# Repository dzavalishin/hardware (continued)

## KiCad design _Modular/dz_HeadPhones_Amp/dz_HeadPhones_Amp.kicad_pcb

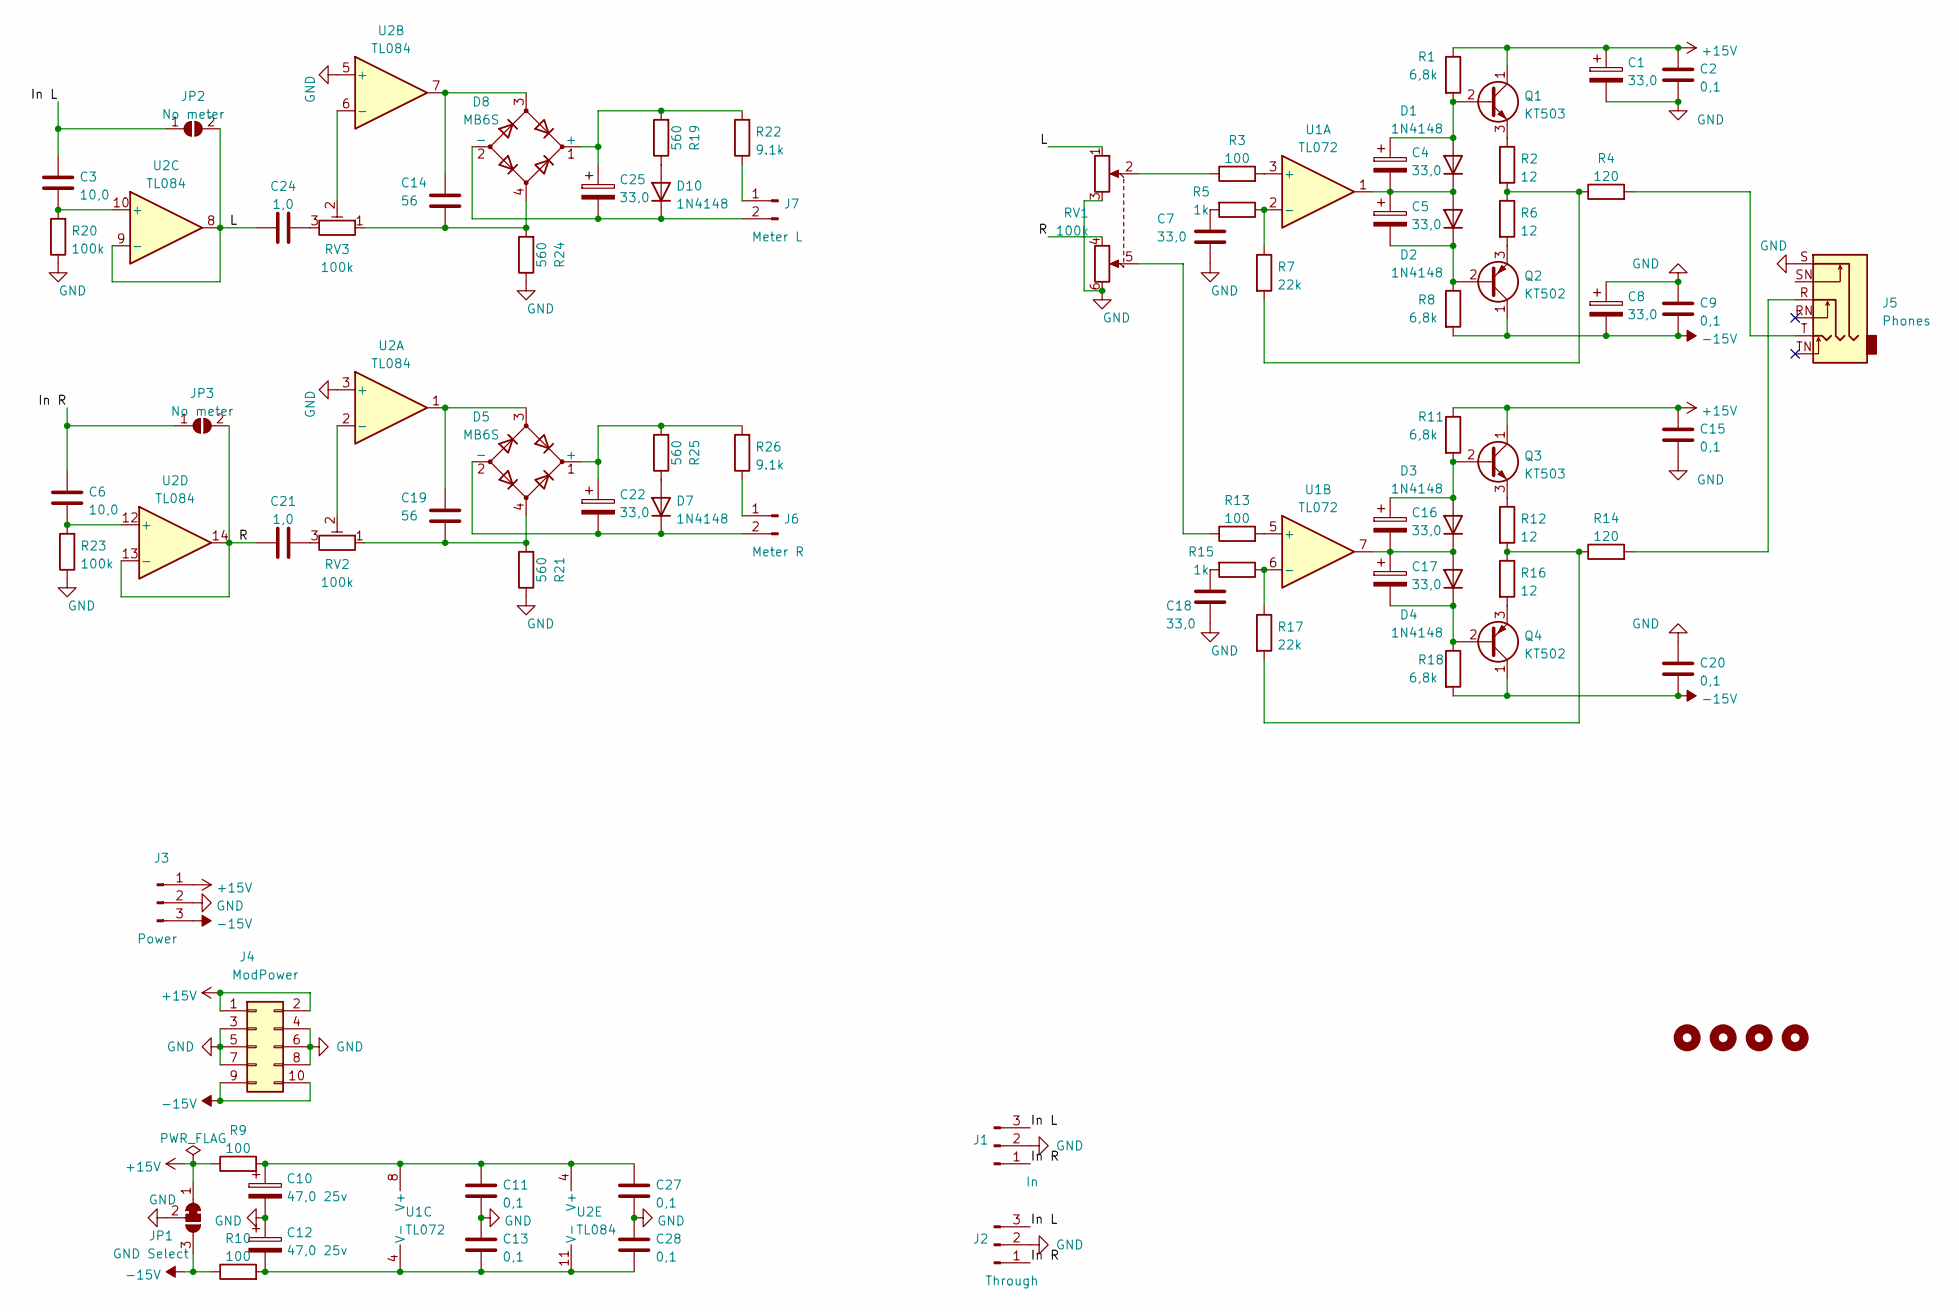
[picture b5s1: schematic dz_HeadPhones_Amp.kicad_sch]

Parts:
C1, C4, C5, C7, C8, C16, C17, C18, C22, C25: 33,0; CP_Radial_D5.0mm_P2.50mm
C2, C9, C11, C13, C15, C20, C27, C28: 0,1; C_1206_3216Metric_Pad1.33x1.80mm_HandSolder
C3, C6: 10,0; C_0805_2012Metric_Pad1.18x1.45mm_HandSolder
C10, C12: 47,0 25v; CP_Radial_D5.0mm_P2.50mm
C14, C19: 56; C_Disc_D5.0mm_W2.5mm_P2.50mm
C21, C24: 1,0; C_0805_2012Metric_Pad1.18x1.45mm_HandSolder
D1, D2, D3, D4, D7, D10: 1N4148; D_DO-35_SOD27_P2.54mm_Vertical_KathodeUp
D5, D8: MB6S; TO-269AA
H1, H2, H3, H4: MountingHole; MountingHole_3.2mm_M3
J1: In; PinHeader_1x03_P2.54mm_Vertical
J2: Through; PinHeader_1x03_P2.54mm_Vertical
J3: Power; PinHeader_1x03_P2.54mm_Vertical
J4: ModPower; PinHeader_2x05_P2.54mm_Vertical
J5: Phones; Jack_6.35mm_Neutrik_NMJ6HCD2_Horizontal
J6: Meter R; PinHeader_1x02_P2.54mm_Vertical
J7: Meter L; PinHeader_1x02_P2.54mm_Vertical
JP1: GND Select; PinHeader_1x03_P2.54mm_Vertical
JP2, JP3: No meter; PinHeader_1x02_P2.54mm_Vertical
Q1, Q3: КТ503; TO-92_Inline
Q2, Q4: КТ502; TO-92_Inline
R1, R8, R11, R18: 6,8k; R_Axial_DIN0207_L6.3mm_D2.5mm_P2.54mm_Vertical
R2, R6, R12, R16: 12; R_Axial_DIN0207_L6.3mm_D2.5mm_P2.54mm_Vertical
R3, R9, R10, R13: 100; R_Axial_DIN0207_L6.3mm_D2.5mm_P2.54mm_Vertical
R4, R14: 120; R_Axial_DIN0207_L6.3mm_D2.5mm_P2.54mm_Vertical
R5, R15: 1k; R_Axial_DIN0207_L6.3mm_D2.5mm_P2.54mm_Vertical
R7, R17: 22k; R_Axial_DIN0207_L6.3mm_D2.5mm_P2.54mm_Vertical
R19, R21, R24, R25: 560; R_Axial_DIN0207_L6.3mm_D2.5mm_P2.54mm_Vertical
R20, R23: 100k; R_Axial_DIN0207_L6.3mm_D2.5mm_P2.54mm_Vertical
R22, R26: 9.1k; R_Axial_DIN0207_L6.3mm_D2.5mm_P2.54mm_Vertical
RV1: 100k; Potentiometer_Alps_RK097_Dual_Horizontal
RV2, RV3: 100k; Potentiometer_Runtron_RM-065_Vertical
U1: TL072; DIP-8_W7.62mm_Socket_LongPads
U2: TL084; DIP-14_W7.62mm_Socket_LongPads

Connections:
+15V: C1.1, C2.1, C15.1, J3.1, J4.1, J4.2, JP1.1 (A), Q1.1 (C), Q3.1 (C), R1.1, R9.1, R11.1
-15V: C8.2, C9.2, C20.2, J3.3, J4.9, J4.10, JP1.3 (B), Q2.1 (C), Q4.1 (C), R8.2, R10.1, R18.2
/In L: C3.1, J1.3, J2.3, JP2.1 (A)
/In R: C6.1, J1.1, J2.1, JP3.1 (A)
/L: C24.1, JP2.2 (B), RV1.1, U2.8, U2.9 (-)
/R: C21.1, JP3.2 (B), RV1.4, U2.13 (-), U2.14
GND: C1.2, C2.2, C7.2, C8.1, C9.1, C10.2, C11.2, C12.1, C13.1, C15.2, C18.2, C20.1, C27.2, C28.1, J1.2, J2.2, J3.2, J4.3, J4.4, J4.5, J4.6, J4.7, J4.8, J5.S, JP1.2 (C), R20.1, R21.1, R23.1, R24.1, RV1.3, RV1.6, U2.3 (+), U2.5 (+)
unnamed: C3.2, R20.2, U2.10 (+)
unnamed: C4.1, D1.2 (A), Q1.2 (B), R1.2
unnamed: C4.2, C5.1, D1.1 (K), D2.2 (A), U1.1
unnamed: C5.2, D2.1 (K), Q2.2 (B), R8.1
unnamed: C6.2, R23.2, U2.12 (+)
unnamed: C7.1, R5.2
unnamed: C10.1, C11.1, C27.1, R9.2, U1.8 (V+), U2.4 (V+)
unnamed: C12.2, C13.2, C28.2, R10.2, U1.4 (V-), U2.11 (V-)
unnamed: C16.1, D3.2 (A), Q3.2 (B), R11.2
unnamed: C16.2, C17.1, D3.1 (K), D4.2 (A), U1.7
unnamed: C17.2, D4.1 (K), Q4.2 (B), R18.1
unnamed: C18.1, R15.2
unnamed: C21.2, RV2.3
unnamed: C22.1, D5.1 (+), R25.2, R26.2
unnamed: C22.2, D5.2 (-), D7.1 (K), J6.2
unnamed: C25.1, D8.1 (+), R19.2, R22.2
unnamed: C25.2, D8.2 (-), D10.1 (K), J7.2
unnamed: C19.1, D5.3, U2.1
unnamed: D7.2 (A), R25.1
unnamed: C14.1, D8.3, U2.7
unnamed: C14.2, D8.4, R24.2, RV3.1
unnamed: D10.2 (A), R19.1
unnamed: J5.R, R14.2
unnamed: J5.T, R4.2
unnamed: J6.1, R26.1
unnamed: J7.1, R22.1
unnamed: Q1.3 (E), R2.1
unnamed: Q2.3 (E), R6.2
unnamed: Q3.3 (E), R12.1
unnamed: Q4.3 (E), R16.2
unnamed: R2.2, R4.1, R6.1, R7.2
unnamed: R3.1, RV1.2
unnamed: R3.2, U1.3 (+)
unnamed: R5.1, R7.1, U1.2 (-)
unnamed: R12.2, R14.1, R16.1, R17.2
unnamed: R13.1, RV1.5
unnamed: R13.2, U1.5 (+)
unnamed: R15.1, R17.1, U1.6 (-)
unnamed: C19.2, D5.4, R21.2, RV2.1
unnamed: RV3.2, U2.6 (-)
unnamed: C24.2, RV3.3
unnamed: RV2.2, U2.2 (-)

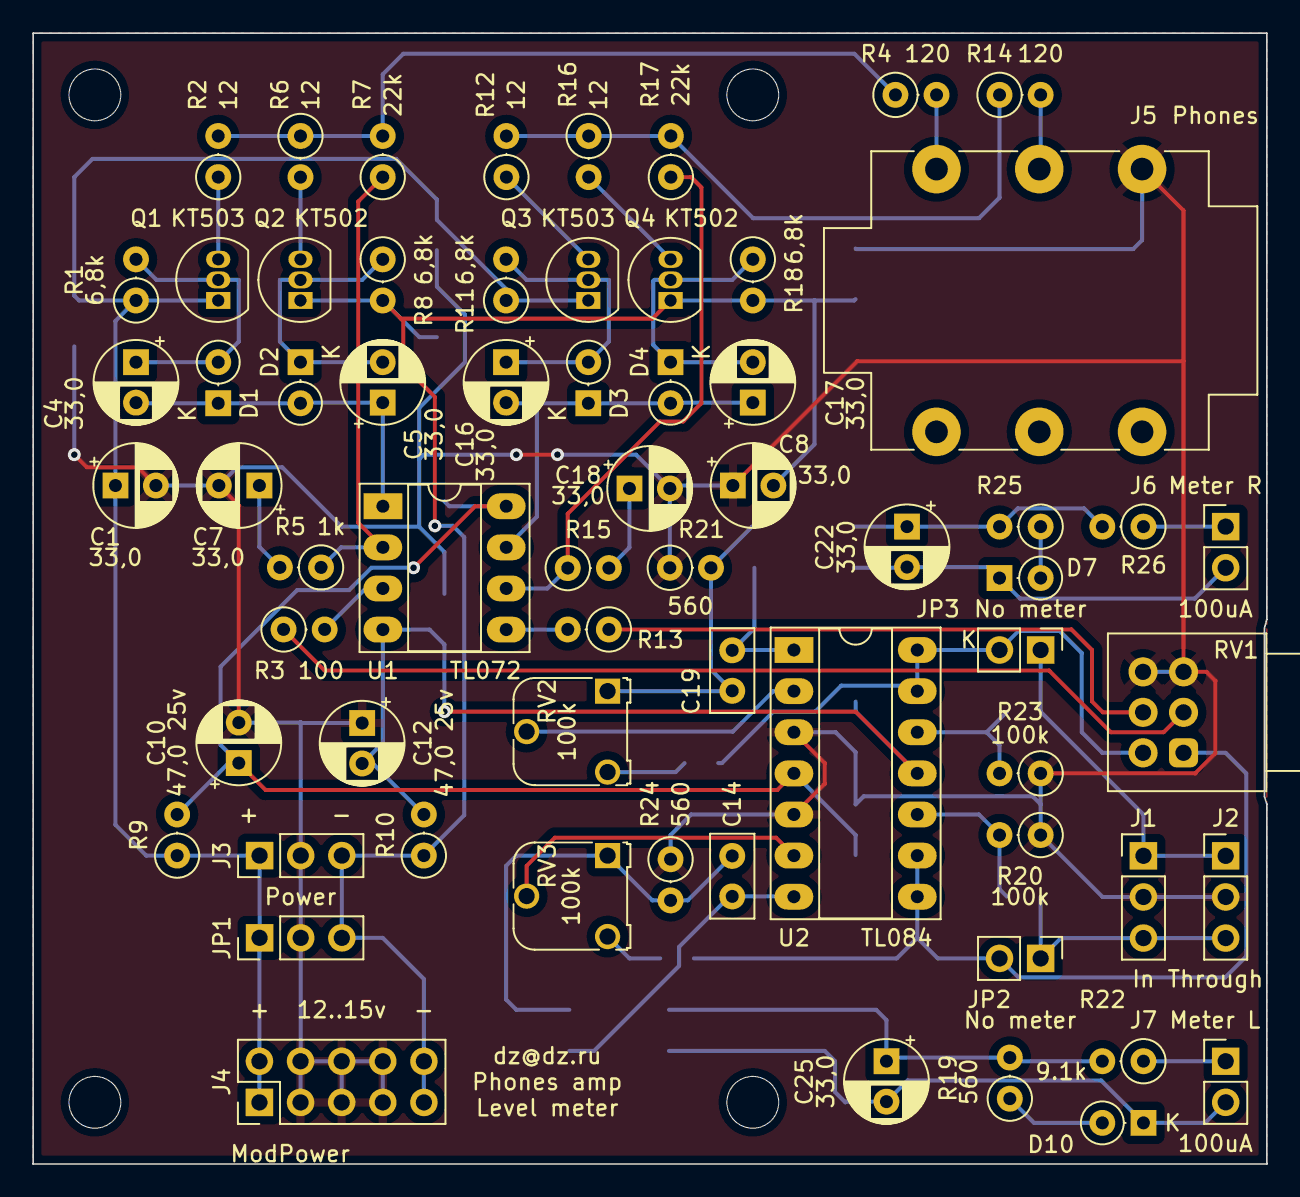
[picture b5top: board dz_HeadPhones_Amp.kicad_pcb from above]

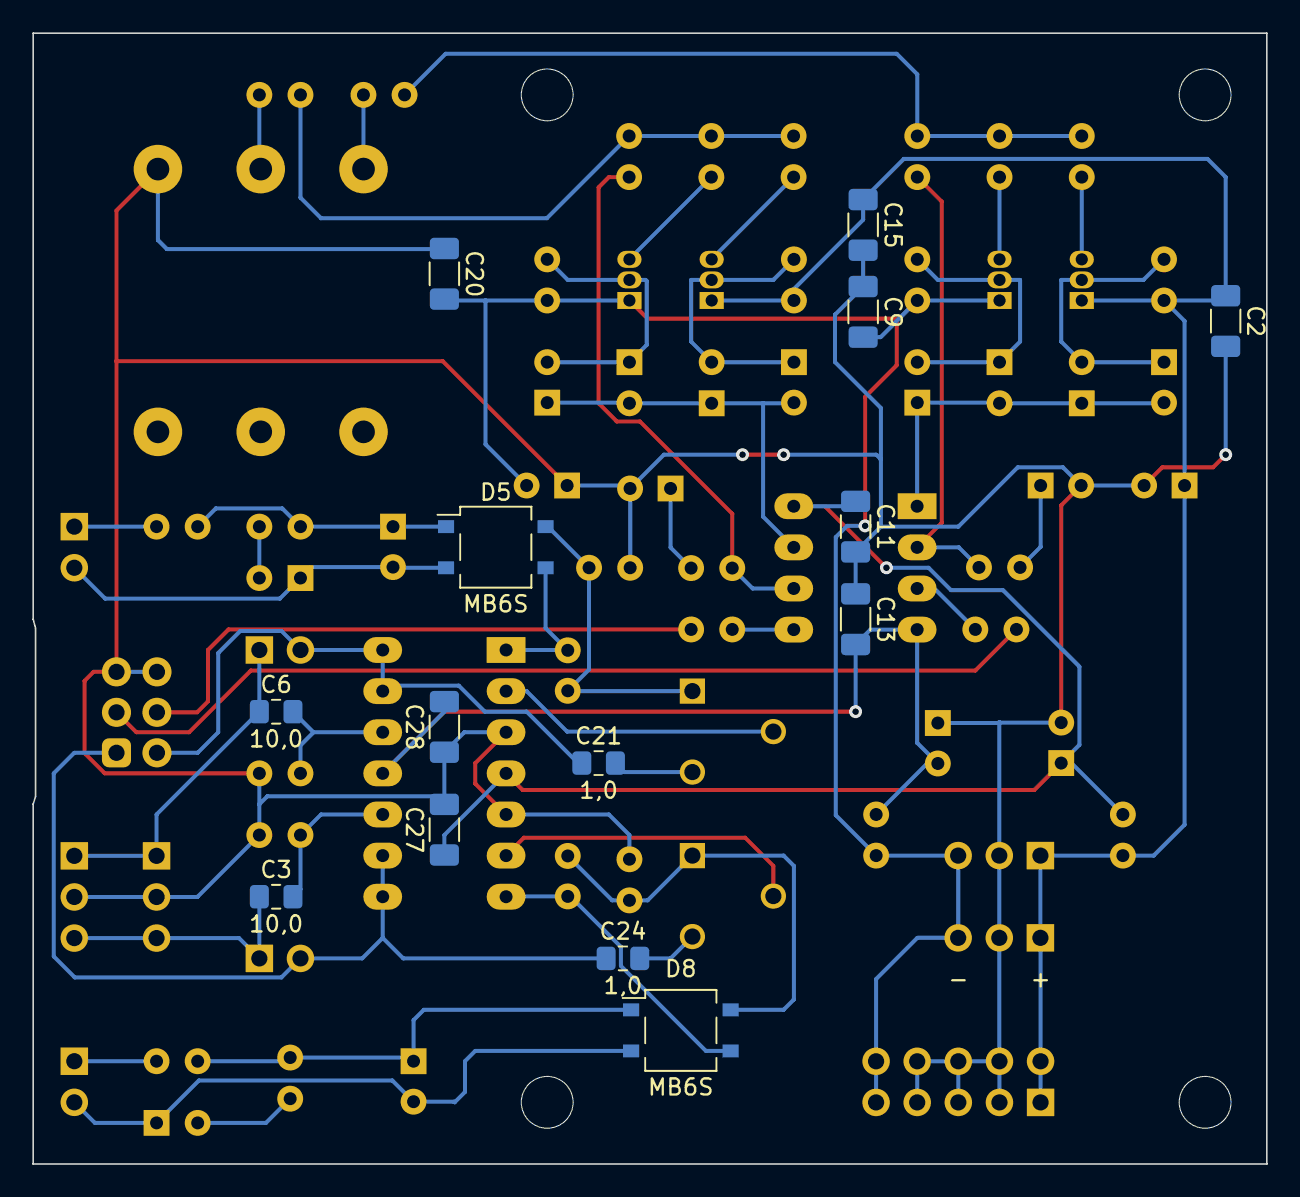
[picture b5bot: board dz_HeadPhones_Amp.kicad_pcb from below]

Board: 2 copper layers, 76.2 x 69.8 mm, 83 parts (14 on the bottom side), 49 nets.

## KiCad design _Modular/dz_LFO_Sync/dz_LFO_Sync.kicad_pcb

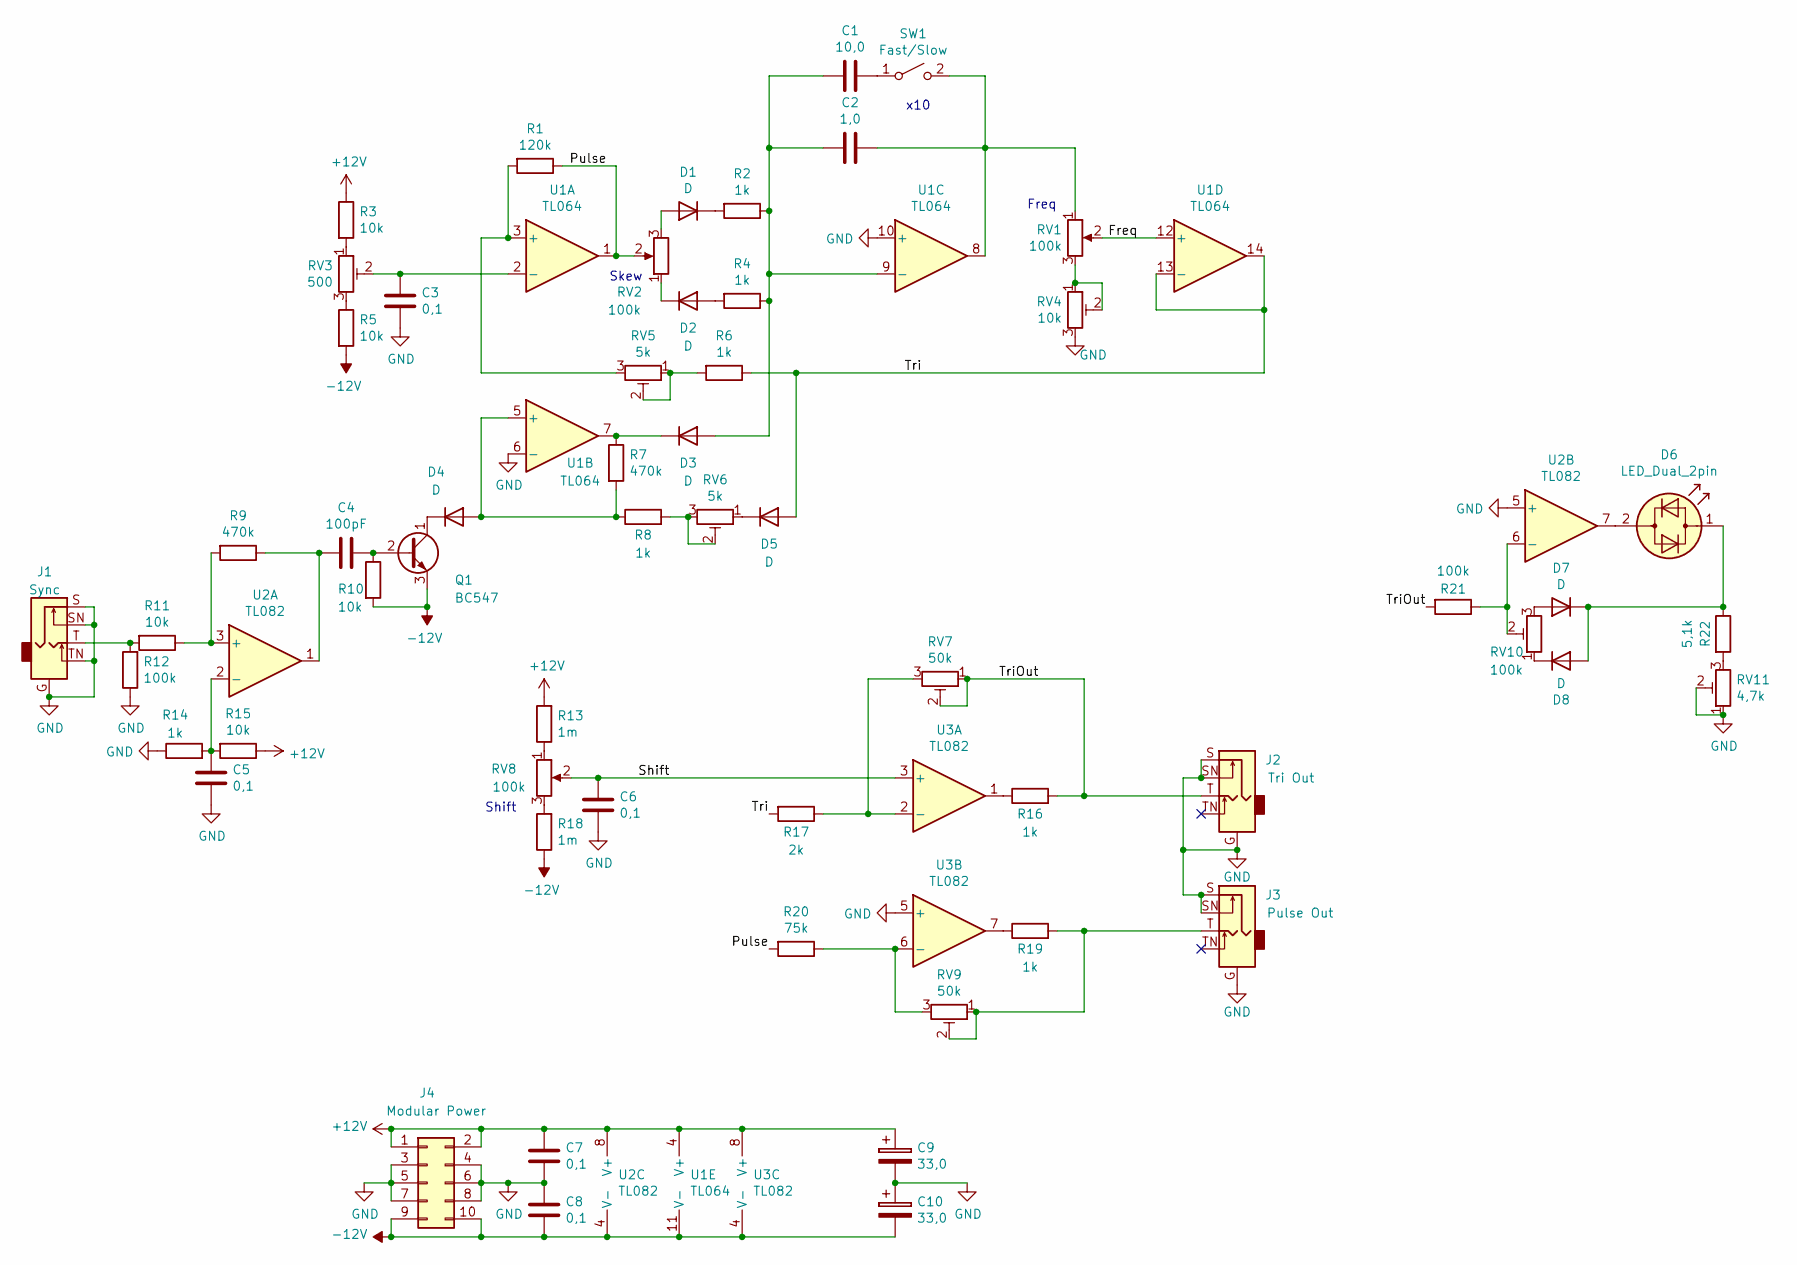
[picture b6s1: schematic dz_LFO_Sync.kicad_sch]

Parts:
C1: 10,0; C_0805_2012Metric_Pad1.18x1.45mm_HandSolder
C2: 1,0; C_0805_2012Metric_Pad1.18x1.45mm_HandSolder
C3, C5, C6, C7, C8: 0,1; C_0805_2012Metric_Pad1.18x1.45mm_HandSolder
C4: 100pF; C_0805_2012Metric_Pad1.18x1.45mm_HandSolder
C9, C10: 33,0; CP_Radial_D7.5mm_P2.50mm
D1, D2, D3, D4, D5, D7, D8: D; D_MicroMELF_Handsoldering
D6: LED_Dual_2pin; LED_D3.0mm_Horizontal_O1.27mm_Z6.0mm
J1: Sync; Jack_3.5mm_CUI_SJ1-3525N_Horizontal
J2: Tri Out; Jack_3.5mm_CUI_SJ1-3525N_Horizontal
J3: Pulse Out; Jack_3.5mm_CUI_SJ1-3525N_Horizontal
J4: Modular Power; PinHeader_2x05_P2.54mm_Vertical
Q1: BC547; TO-92_Inline
R1: 120k; R_0805_2012Metric_Pad1.20x1.40mm_HandSolder
R2, R4, R6, R8, R14, R16, R19: 1k; R_0805_2012Metric_Pad1.20x1.40mm_HandSolder
R3, R5, R10, R11, R15: 10k; R_0805_2012Metric_Pad1.20x1.40mm_HandSolder
R7, R9: 470k; R_0805_2012Metric_Pad1.20x1.40mm_HandSolder
R12, R21: 100k; R_0805_2012Metric_Pad1.20x1.40mm_HandSolder
R13, R18: 1m; R_0805_2012Metric_Pad1.20x1.40mm_HandSolder
R17: 2k; R_0805_2012Metric_Pad1.20x1.40mm_HandSolder
R20: 75k; R_0805_2012Metric_Pad1.20x1.40mm_HandSolder
R22: 5,1k; R_0805_2012Metric_Pad1.20x1.40mm_HandSolder
RV1, RV2, RV8: 100k; Potentiometer_Alps_RK097_Single_Horizontal
RV3: 500; Potentiometer_Runtron_RM-065_Vertical
RV4: 10k; Potentiometer_Runtron_RM-065_Vertical
RV5, RV6: 5k; Potentiometer_Runtron_RM-065_Vertical
RV7, RV9: 50k; Potentiometer_Runtron_RM-065_Vertical
RV10: 100k; Potentiometer_Runtron_RM-065_Vertical
RV11: 4,7k; Potentiometer_Runtron_RM-065_Vertical
SW1: Fast/Slow; PinHeader_1x02_P2.54mm_Vertical
U1: TL064; DIP-14_W7.62mm_Socket_LongPads
U2, U3: TL082; DIP-8_W7.62mm_Socket_LongPads

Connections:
+12V: C7.1, C9.1, J4.1, J4.2, R3.1, R13.2, R15.1, U1.4 (V+), U2.8 (V+), U3.8 (V+)
-12V: C8.2, C10.2, J4.9, J4.10, Q1.3 (E), R5.2, R10.2, R18.1, U1.11 (V-), U2.4 (V-), U3.4 (V-)
/Freq: RV1.2, U1.12 (+)
/Pulse: R1.1, R20.2, RV2.2, U1.1
/Shift: C6.1, RV8.2, U3.3 (+)
/Tri: D5.2 (A), R6.1, R17.2, U1.13 (-), U1.14
/TriOut: J2.T, R16.2, R21.2, RV7.1, RV7.2
GND: C3.2, C5.2, C6.2, C7.2, C8.1, C9.2, C10.1, J1.G, J1.S, J1.SN, J1.TN, J2.G, J2.S, J2.SN, J3.G, J3.S, J3.SN, J4.3, J4.4, J4.5, J4.6, J4.7, J4.8, R12.1, R14.1, RV4.3, RV11.1, RV11.2, U1.6 (-), U1.10 (+), U2.5 (+), U3.5 (+)
unnamed: C1.1, SW1.1 (A)
unnamed: C1.2, C2.2, D3.2 (A), R2.1, R4.1, U1.9 (-)
unnamed: C2.1, RV1.1, SW1.2 (B), U1.8
unnamed: C3.1, RV3.2, U1.2 (-)
unnamed: C4.1, Q1.2 (B), R10.1
unnamed: C4.2, R9.1, U2.1
unnamed: C5.1, R14.2, R15.2, U2.2 (-)
unnamed: D1.1 (K), R2.2
unnamed: D1.2 (A), RV2.3
unnamed: D2.1 (K), RV2.1
unnamed: D2.2 (A), R4.2
unnamed: D3.1 (K), R7.1, U1.7
unnamed: D4.1 (K), Q1.1 (C)
unnamed: D4.2 (A), R7.2, R8.1, U1.5 (+)
unnamed: D5.1 (K), RV6.1
unnamed: D6.1 (KA), D7.1 (K), D8.2 (A), R22.1
unnamed: D6.2 (AK), U2.7
unnamed: D7.2 (A), RV10.3
unnamed: D8.1 (K), RV10.1
unnamed: R1.2, RV5.3, U1.3 (+)
unnamed: R3.2, RV3.1
unnamed: R5.1, RV3.3
unnamed: R6.2, RV5.1, RV5.2
unnamed: R8.2, RV6.2, RV6.3
unnamed: R9.2, R11.1, U2.3 (+)
unnamed: J1.T, R11.2, R12.2
unnamed: R13.1, RV8.1
unnamed: R16.1, U3.1
unnamed: R17.1, RV7.3, U3.2 (-)
unnamed: R18.2, RV8.3
unnamed: R19.1, U3.7
unnamed: J3.T, R19.2, RV9.1, RV9.2
unnamed: R20.1, RV9.3, U3.6 (-)
unnamed: R21.1, RV10.2, U2.6 (-)
unnamed: R22.2, RV11.3
unnamed: RV1.3, RV4.1, RV4.2

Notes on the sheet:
Shift
Freq
Skew
x10

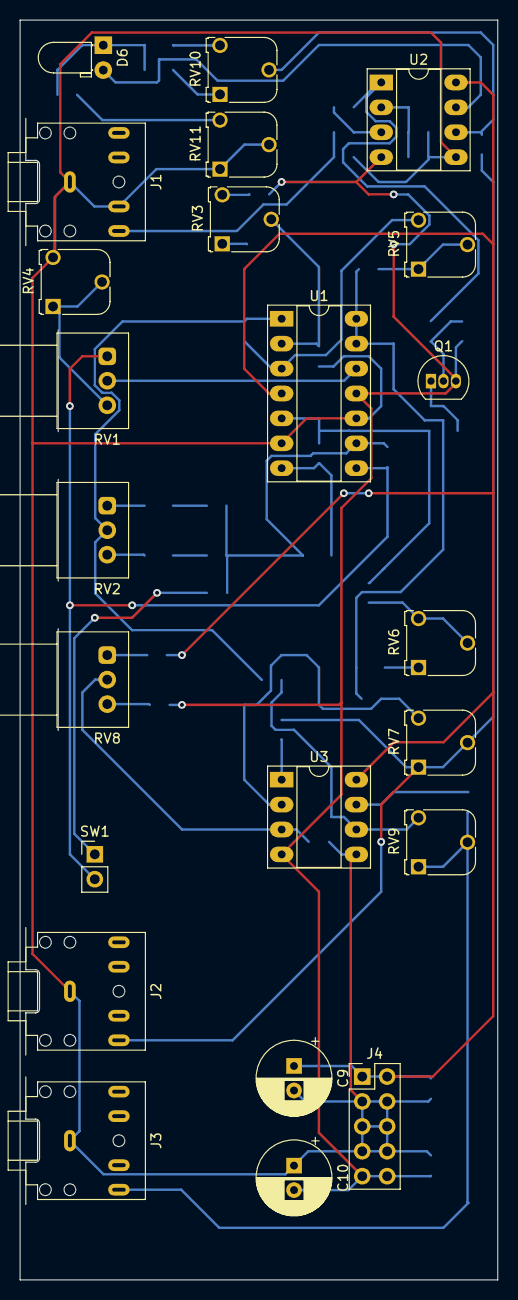
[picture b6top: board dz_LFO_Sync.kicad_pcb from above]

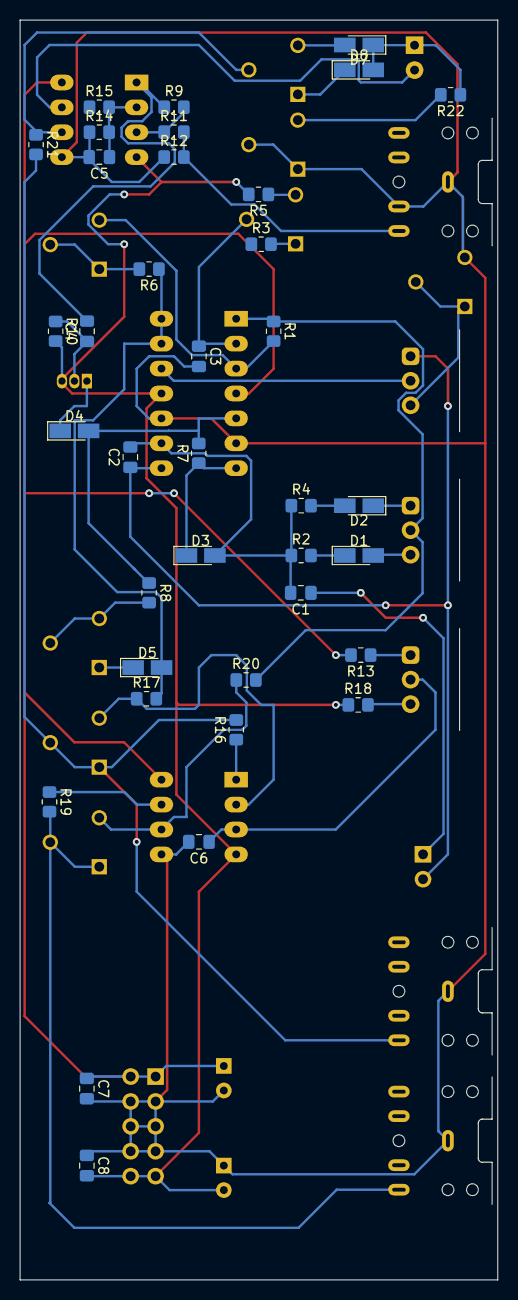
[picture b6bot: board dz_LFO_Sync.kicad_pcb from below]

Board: 2 copper layers, 48.7 x 128.5 mm, 60 parts (37 on the bottom side), 44 nets.

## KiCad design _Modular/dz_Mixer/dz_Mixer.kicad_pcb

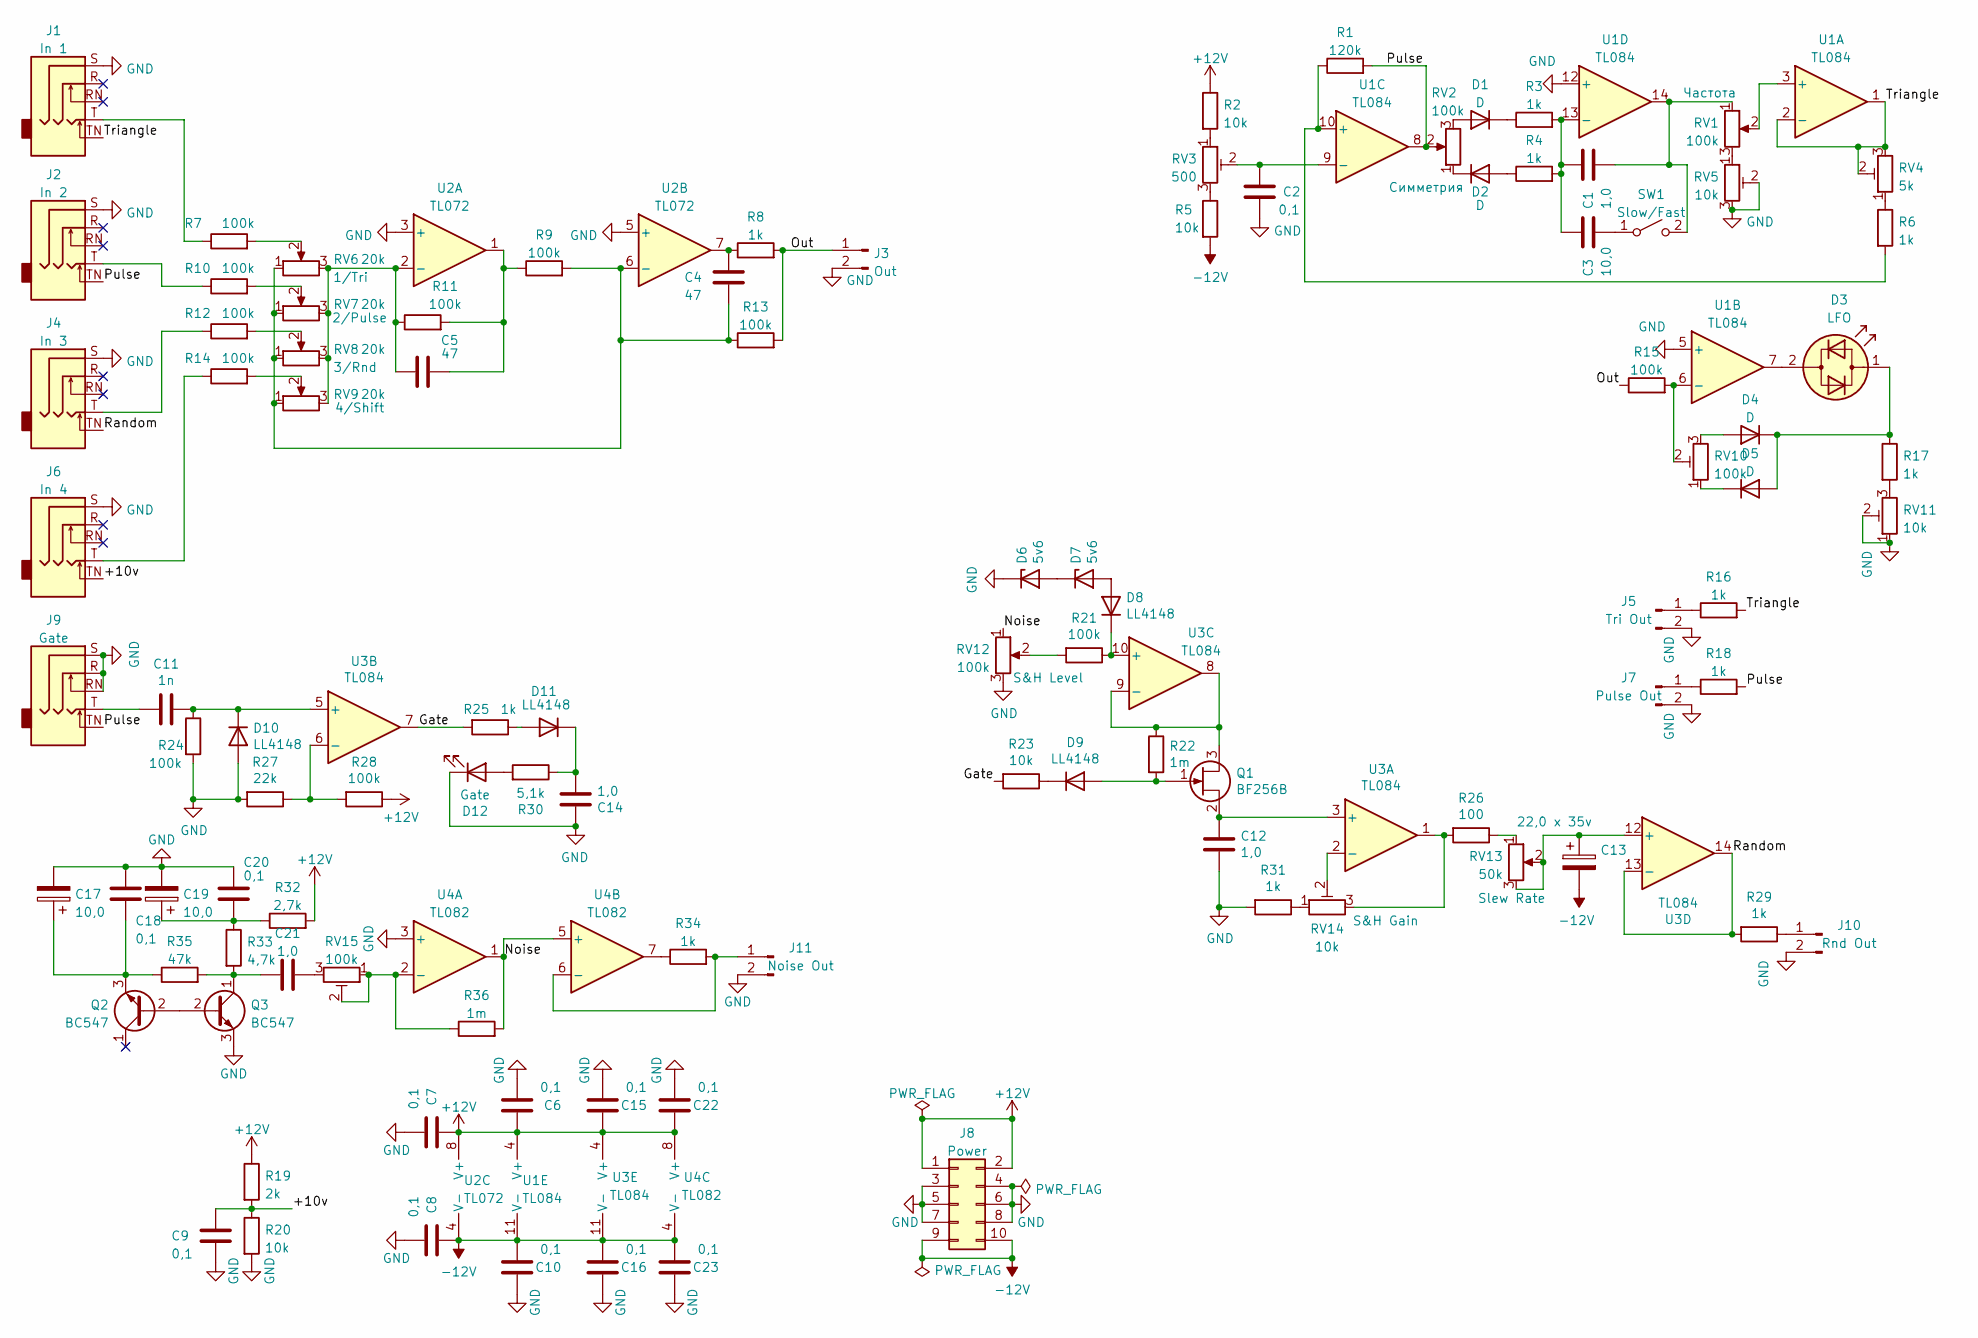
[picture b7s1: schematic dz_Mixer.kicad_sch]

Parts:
C1, C12, C14, C21: 1,0; C_1206_3216Metric_Pad1.33x1.80mm_HandSolder
C2, C6, C7, C8, C9, C10, C15, C16, C18, C20, C22, C23: 0,1; C_1206_3216Metric_Pad1.33x1.80mm_HandSolder
C3: 10,0; C_0805_2012Metric_Pad1.18x1.45mm_HandSolder
C4, C5: 47; C_1206_3216Metric_Pad1.33x1.80mm_HandSolder
C11: 1n; C_1206_3216Metric_Pad1.33x1.80mm_HandSolder
C13: 22,0 x 35v; CP_Radial_D8.0mm_P2.50mm
C17, C19: 10,0; CP_Elec_4x5.4
D1, D2, D4, D5: D; D_MiniMELF_Handsoldering
D3: LFO; LED_D3.0mm
D6, D7: 5v6; D_MiniMELF_Handsoldering
D8, D9, D10, D11: LL4148; D_MiniMELF_Handsoldering
D12: Gate; LED_D3.0mm_Horizontal_O1.27mm_Z2.0mm
J1: In 1; Jack_3.5mm_CUI_SJ1-3525N_Horizontal
J2: In 2; Jack_3.5mm_CUI_SJ1-3525N_Horizontal
J3: Out; PinHeader_1x02_P2.54mm_Vertical
J4: In 3; Jack_3.5mm_CUI_SJ1-3525N_Horizontal
J5: Tri Out; PinHeader_1x02_P2.54mm_Vertical
J6: In 4; Jack_3.5mm_CUI_SJ1-3525N_Horizontal
J7: Pulse Out; PinHeader_1x02_P2.54mm_Vertical
J8: Power; PinHeader_2x05_P2.54mm_Vertical
J9: Gate; Jack_3.5mm_CUI_SJ1-3525N_Horizontal
J10: Rnd Out; PinHeader_1x02_P2.54mm_Vertical
J11: Noise Out; PinHeader_1x02_P2.54mm_Vertical
Q1: BF256B; TO-92
Q2, Q3: BC547; TO-92
R1: 120k; R_1206_3216Metric_Pad1.30x1.75mm_HandSolder
R2, R5, R20, R23: 10k; R_1206_3216Metric_Pad1.30x1.75mm_HandSolder
R3, R4, R6, R8, R16, R17, R18, R25, R29, R31, R34: 1k; R_1206_3216Metric_Pad1.30x1.75mm_HandSolder
R7, R9, R10, R11, R12, R13, R14, R15, R21, R24, R28: 100k; R_1206_3216Metric_Pad1.30x1.75mm_HandSolder
R19: 2k; R_1206_3216Metric_Pad1.30x1.75mm_HandSolder
R22, R36: 1m; R_1206_3216Metric_Pad1.30x1.75mm_HandSolder
R26: 100; R_1206_3216Metric_Pad1.30x1.75mm_HandSolder
R27: 22k; R_1206_3216Metric_Pad1.30x1.75mm_HandSolder
R30: 5,1k; R_1206_3216Metric_Pad1.30x1.75mm_HandSolder
R32: 2,7k; R_1206_3216Metric_Pad1.30x1.75mm_HandSolder
R33: 4,7k; R_1206_3216Metric_Pad1.30x1.75mm_HandSolder
R35: 47k; R_1206_3216Metric_Pad1.30x1.75mm_HandSolder
RV1, RV2, RV12: 100k; PinHeader_1x03_P2.54mm_Vertical
RV3: 500; Potentiometer_Runtron_RM-065_Vertical
RV4: 5k; Potentiometer_Runtron_RM-065_Vertical
RV5, RV11, RV14: 10k; Potentiometer_Runtron_RM-065_Vertical
RV6, RV7, RV8, RV9: 20k; PinHeader_1x03_P2.54mm_Vertical
RV10, RV15: 100k; Potentiometer_Runtron_RM-065_Vertical
RV13: 50k; PinHeader_1x03_P2.54mm_Vertical
SW1: Slow/Fast; PinHeader_1x02_P2.54mm_Vertical
U1, U3: TL084; DIP-14_W7.62mm_Socket_LongPads
U2: TL072; DIP-8_W7.62mm_Socket_LongPads
U4: TL082; DIP-8_W7.62mm_Socket_LongPads

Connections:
+12V: C6.2, C7.2, C15.2, C22.2, J8.1, J8.2, R2.1, R19.1, R28.1, R32.2, U1.4 (V+), U2.8 (V+), U3.4 (V+), U4.8 (V+)
-12V: C8.2, C10.1, C13.2, C16.1, C23.1, J8.9, J8.10, R5.2, U1.11 (V-), U2.4 (V-), U3.11 (V-), U4.4 (V-)
/+10v: C9.2, J6.TN, R19.2, R20.1
/Gate: R23.2, R25.2, U3.7
/Noise: R36.2, RV12.1, U4.1, U4.5 (+)
/Out: J3.1, R8.2, R13.2, R15.1
/Pulse: J2.TN, J9.TN, R1.2, R18.2, RV2.2, U1.8
/Random: J4.TN, R29.2, U3.13 (-), U3.14
/Triangle: J1.TN, R16.2, RV4.2, RV4.3, U1.1, U1.2 (-)
GND: C2.1, C6.1, C7.1, C8.1, C9.1, C10.2, C12.2, C14.1, C15.1, C16.2, C17.2, C18.1, C19.2, C20.1, C22.1, C23.2, D6.1 (K), D10.2 (A), D12.1 (K), J1.S, J2.S, J3.2, J4.S, J5.2, J6.S, J7.2, J8.3, J8.4, J8.5, J8.6, J8.7, J8.8, J9.R, J9.RN, J9.S, J10.2, J11.2, Q3.3 (E), R20.2, R24.2, R27.2, R31.2, RV5.2, RV5.3, RV11.1, RV11.2, RV12.3, U1.5 (+), U1.12 (+), U2.3 (+), U2.5 (+), U4.3 (+)
unnamed: C1.1, RV1.1, SW1.2 (B), U1.14
unnamed: C1.2, C3.2, R3.2, R4.2, U1.13 (-)
unnamed: C2.2, RV3.2, U1.9 (-)
unnamed: C3.1, SW1.1 (A)
unnamed: C4.1, R9.2, R13.1, RV6.1, RV7.1, RV8.1, RV9.1, U2.6 (-)
unnamed: C4.2, R8.1, U2.7
unnamed: C5.1, R11.1, RV6.3, RV7.3, RV8.3, RV9.3, U2.2 (-)
unnamed: C5.2, R9.1, R11.2, U2.1
unnamed: C11.1, D10.1 (K), R24.1, U3.5 (+)
unnamed: C11.2, J9.T
unnamed: C12.1, Q1.2 (S), U3.3 (+)
unnamed: C13.1, RV13.2, RV13.3, U3.12 (+)
unnamed: C14.2, D11.1 (K), R30.1
unnamed: C17.1, C18.2, Q2.3 (E), R35.1
unnamed: C19.1, C20.2, R32.1, R33.1
unnamed: C21.1, Q3.1 (C), R33.2, R35.2
unnamed: C21.2, RV15.3
unnamed: D1.1 (K), R3.1
unnamed: D1.2 (A), RV2.3
unnamed: D2.1 (K), RV2.1
unnamed: D2.2 (A), R4.1
unnamed: D3.1 (KA), D4.1 (K), D5.2 (A), R17.1
unnamed: D3.2 (AK), U1.7
unnamed: D4.2 (A), RV10.3
unnamed: D5.1 (K), RV10.1
unnamed: D6.2 (A), D7.1 (K)
unnamed: D7.2 (A), D8.2 (A)
unnamed: D8.1 (K), R21.1, U3.10 (+)
unnamed: D9.1 (K), R23.1
unnamed: D9.2 (A), Q1.1 (G), R22.2
unnamed: D11.2 (A), R25.1
unnamed: D12.2 (A), R30.2
unnamed: J1.T, R7.1
unnamed: J2.T, R10.1
unnamed: J4.T, R12.1
unnamed: J5.1, R16.1
unnamed: J6.T, R14.1
unnamed: J7.1, R18.1
unnamed: J11.1, R34.2, U4.6 (-)
unnamed: Q1.3 (D), R22.1, U3.8, U3.9 (-)
unnamed: Q2.2 (B), Q3.2 (B)
unnamed: R1.1, R6.2, U1.10 (+)
unnamed: R2.2, RV3.1
unnamed: R5.1, RV3.3
unnamed: R6.1, RV4.1
unnamed: R7.2, RV6.2
unnamed: R10.2, RV7.2
unnamed: R12.2, RV8.2
unnamed: R14.2, RV9.2
unnamed: R15.2, RV10.2, U1.6 (-)
unnamed: R17.2, RV11.3
unnamed: R26.1, RV13.1
unnamed: R26.2, RV14.3, U3.1
unnamed: R27.1, R28.2, U3.6 (-)
unnamed: J10.1, R29.1
unnamed: R31.1, RV14.1
unnamed: R34.1, U4.7
unnamed: R36.1, RV15.1, RV15.2, U4.2 (-)
unnamed: RV1.2, U1.3 (+)
unnamed: RV1.3, RV5.1
unnamed: R21.2, RV12.2
unnamed: RV14.2, U3.2 (-)

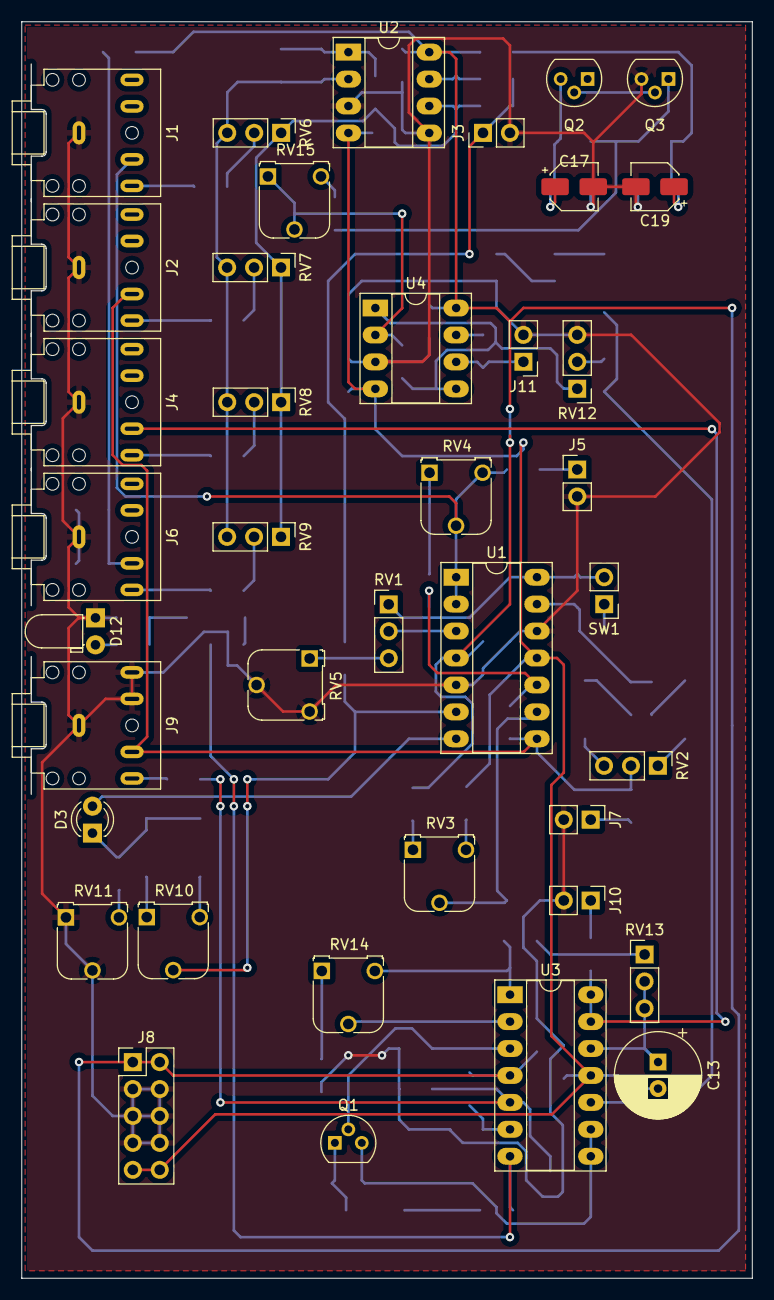
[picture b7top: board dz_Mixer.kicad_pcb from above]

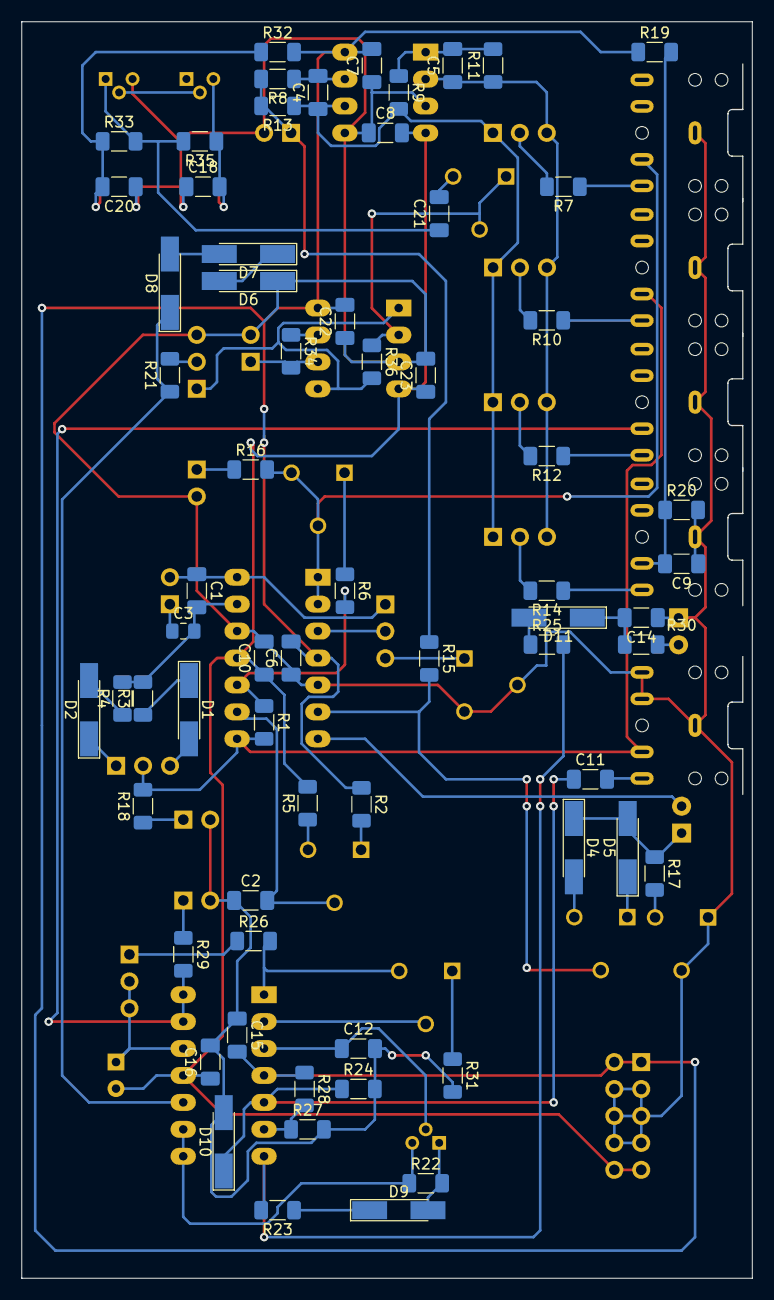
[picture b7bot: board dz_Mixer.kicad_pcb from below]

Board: 2 copper layers, 68.9 x 118.5 mm, 105 parts (66 on the bottom side), 72 nets.
